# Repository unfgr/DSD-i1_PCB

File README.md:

# DSD-i1_PCB
DSD-i1 DEV/EDU Board Design

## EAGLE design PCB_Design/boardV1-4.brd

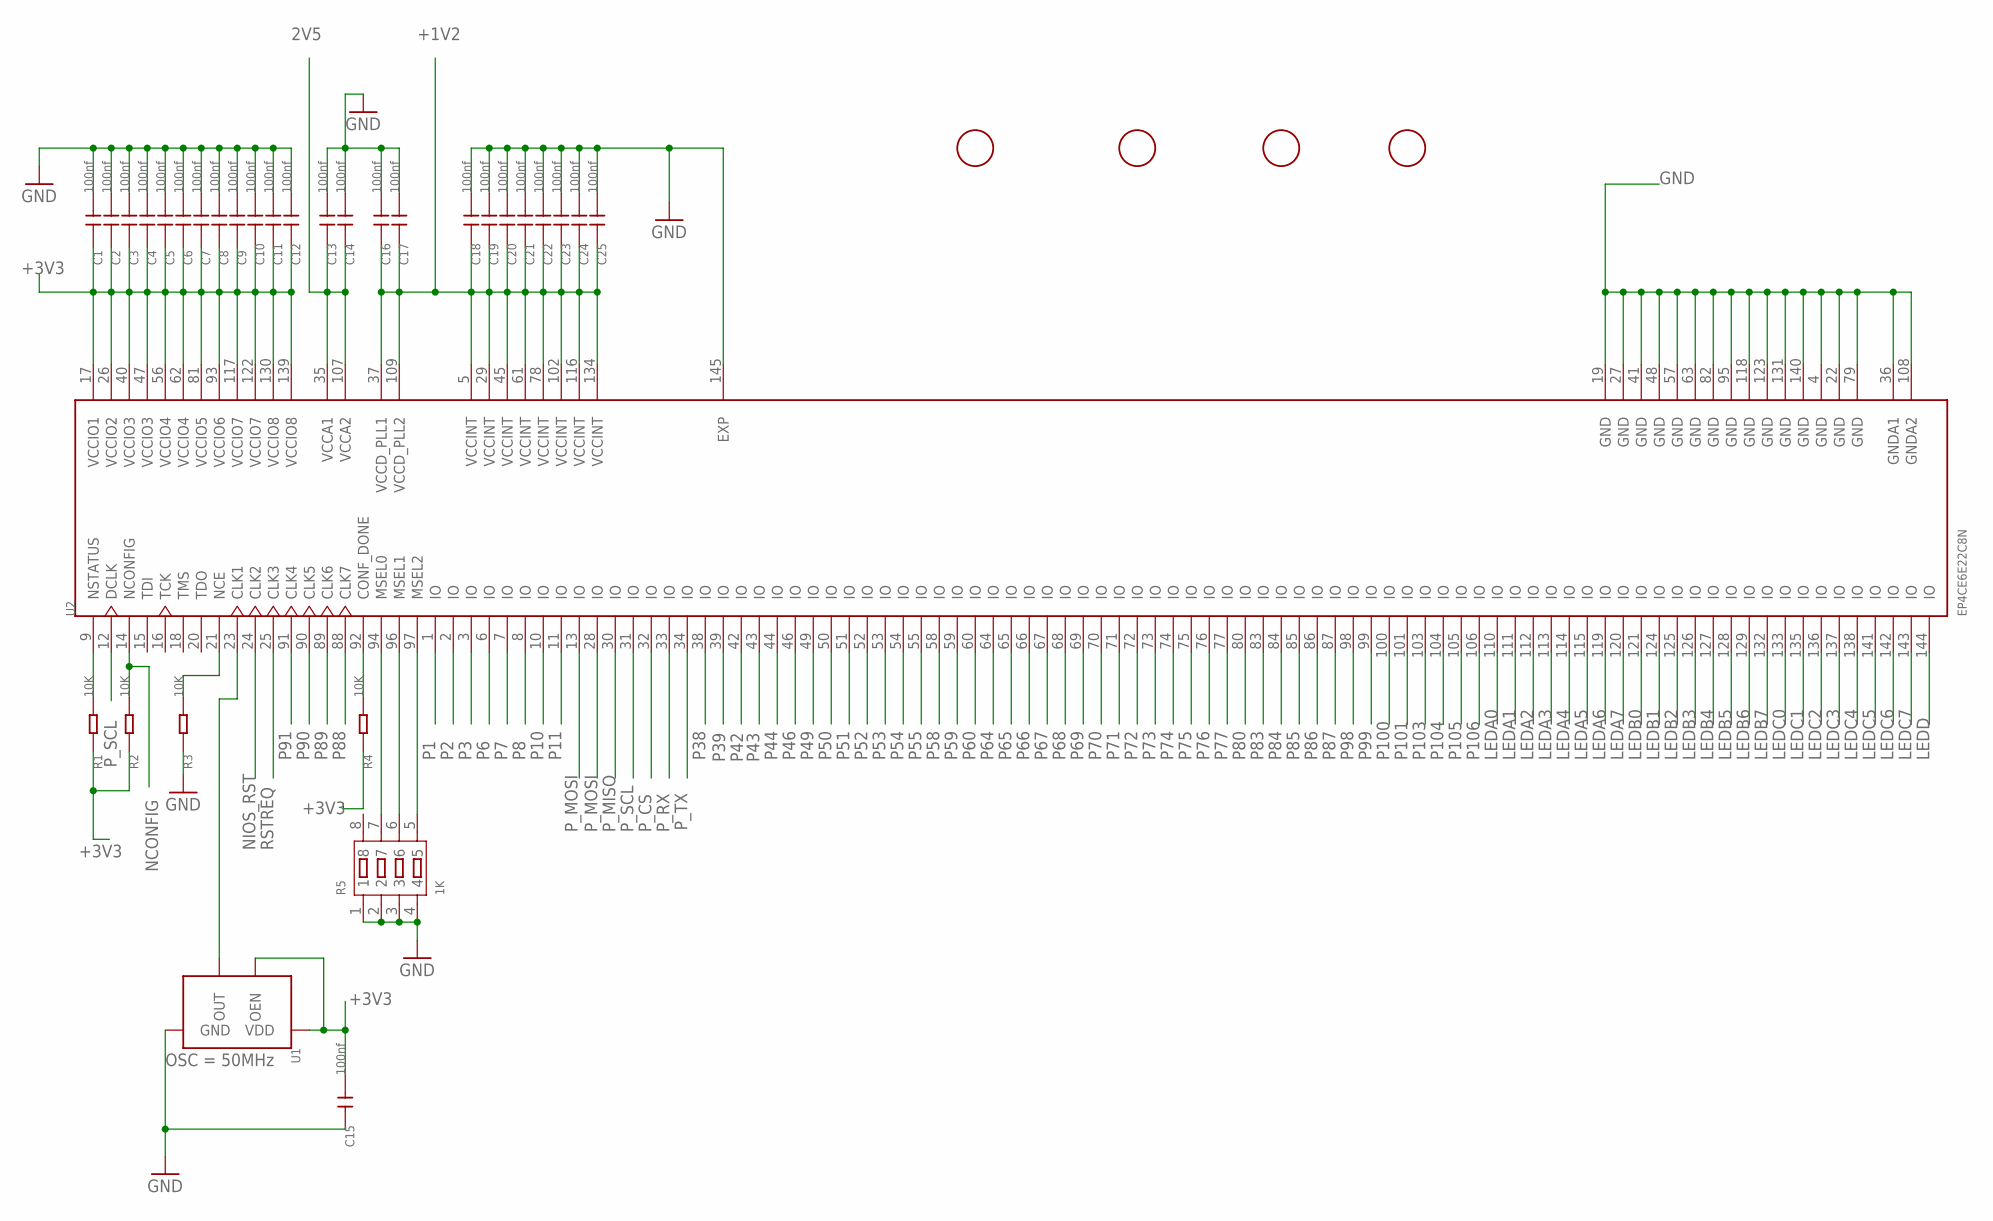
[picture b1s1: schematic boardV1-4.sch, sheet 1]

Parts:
C1, C2, C3, C4, C5, C6, C7, C8, C9, C10, C11, C12, C13, C14, C15, C16, C17, C18, C19, C20, C21, C22, C23, C24, C25: 100nf; C0603
R1, R2, R3, R4: 10K; R0603
R5: 1K; RA1206-8
U1: 306020041_OSC_32.768KHZ-3225_4P; X3225_4P
U2: EP4CE6E22C8N; QFP50P2200X2200X165-145N
U$1, U$2, U$3, U$4: FIDUCIAL; FIDUCIAL_1MM

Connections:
2V5: C13.1, C14.1, U2.35 (VCCA1), U2.107 (VCCA2); also elsewhere on the board
+1V2: C16.1, C17.1, C18.1, C19.1, C20.1, C21.1, C22.1, C23.1, C24.1, C25.1, U2.5 (VCCINT), U2.29 (VCCINT), U2.37 (VCCD_PLL1), U2.45 (VCCINT), U2.61 (VCCINT), U2.78 (VCCINT), U2.102 (VCCINT), U2.109 (VCCD_PLL2), U2.116 (VCCINT), U2.134 (VCCINT); also elsewhere on the board
+3V3: C1.1, C2.1, C3.1, C4.1, C5.1, C6.1, C7.1, C8.1, C9.1, C10.1, C11.1, C12.1, C15.2, R1.1, R2.1, R4.1, U1.P$1 (OEN), U1.P$4 (VDD), U2.17 (VCCIO1), U2.26 (VCCIO2), U2.40 (VCCIO3), U2.47 (VCCIO3), U2.56 (VCCIO4), U2.62 (VCCIO4), U2.81 (VCCIO5), U2.93 (VCCIO6), U2.117 (VCCIO7), U2.122 (VCCIO7), U2.130 (VCCIO8), U2.139 (VCCIO8); also elsewhere on the board
GND: C1.2, C2.2, C3.2, C4.2, C5.2, C6.2, C7.2, C8.2, C9.2, C10.2, C11.2, C12.2, C13.2, C14.2, C15.1, C16.2, C17.2, C18.2, C19.2, C20.2, C21.2, C22.2, C23.2, C24.2, C25.2, R3.1, R5.1, R5.2, R5.3, R5.4, U1.P$2 (GND), U2.4 (GND), U2.19 (GND), U2.22 (GND), U2.27 (GND), U2.36 (GNDA1), U2.41 (GND), U2.48 (GND), U2.57 (GND), U2.63 (GND), U2.79 (GND), U2.82 (GND), U2.95 (GND), U2.108 (GNDA2), U2.118 (GND), U2.123 (GND), U2.131 (GND), U2.140 (GND), U2.145 (EXP); also elsewhere on the board
LEDA0: U2.110 (IO); also elsewhere on the board
LEDA1: U2.111 (IO); also elsewhere on the board
LEDA2: U2.112 (IO); also elsewhere on the board
LEDA3: U2.113 (IO); also elsewhere on the board
LEDA4: U2.114 (IO); also elsewhere on the board
LEDA5: U2.115 (IO); also elsewhere on the board
LEDA6: U2.119 (IO); also elsewhere on the board
LEDA7: U2.120 (IO); also elsewhere on the board
LEDB0: U2.121 (IO); also elsewhere on the board
LEDB1: U2.124 (IO); also elsewhere on the board
LEDB2: U2.125 (IO); also elsewhere on the board
LEDB3: U2.126 (IO); also elsewhere on the board
LEDB4: U2.127 (IO); also elsewhere on the board
LEDB5: U2.128 (IO); also elsewhere on the board
LEDB6: U2.129 (IO); also elsewhere on the board
LEDB7: U2.132 (IO); also elsewhere on the board
LEDC0: U2.133 (IO); also elsewhere on the board
LEDC1: U2.135 (IO); also elsewhere on the board
LEDC2: U2.136 (IO); also elsewhere on the board
LEDC3: U2.137 (IO); also elsewhere on the board
LEDC4: U2.138 (IO); also elsewhere on the board
LEDC5: U2.141 (IO); also elsewhere on the board
LEDC6: U2.142 (IO); also elsewhere on the board
LEDC7: U2.143 (IO); also elsewhere on the board
LEDD: U2.144 (IO); also elsewhere on the board
unnamed: R4.2, U2.92 (CONF_DONE)
unnamed: U1.P$3 (OUT), U2.23 (CLK1)
unnamed: R5.5, U2.97 (MSEL2)
unnamed: R5.6, U2.96 (MSEL1)
unnamed: R5.7, U2.94 (MSEL0)
unnamed: R3.2, U2.21 (NCE)
unnamed: R1.2, U2.9 (NSTATUS)
NCONFIG: R2.2, U2.14 (NCONFIG); also elsewhere on the board
NIOS_RST: U2.24 (CLK2); also elsewhere on the board
P1: U2.1 (IO); also elsewhere on the board
P2: U2.2 (IO); also elsewhere on the board
P3: U2.3 (IO); also elsewhere on the board
P6: U2.6 (IO); also elsewhere on the board
P7: U2.7 (IO); also elsewhere on the board
P8: U2.8 (IO); also elsewhere on the board
P10: U2.10 (IO); also elsewhere on the board
P11: U2.11 (IO); also elsewhere on the board
P38: U2.38 (IO); also elsewhere on the board
P39: U2.39 (IO); also elsewhere on the board
P42: U2.42 (IO); also elsewhere on the board
P43: U2.43 (IO); also elsewhere on the board
P44: U2.44 (IO); also elsewhere on the board
P46: U2.46 (IO); also elsewhere on the board
P49: U2.49 (IO); also elsewhere on the board
P50: U2.50 (IO); also elsewhere on the board
P51: U2.51 (IO); also elsewhere on the board
P52: U2.52 (IO); also elsewhere on the board
P53: U2.53 (IO); also elsewhere on the board
P54: U2.54 (IO); also elsewhere on the board
P55: U2.55 (IO); also elsewhere on the board
P58: U2.58 (IO); also elsewhere on the board
P59: U2.59 (IO); also elsewhere on the board
P60: U2.60 (IO); also elsewhere on the board
P64: U2.64 (IO); also elsewhere on the board
P65: U2.65 (IO); also elsewhere on the board
P66: U2.66 (IO); also elsewhere on the board
P67: U2.67 (IO); also elsewhere on the board
P68: U2.68 (IO); also elsewhere on the board
P69: U2.69 (IO); also elsewhere on the board
P70: U2.70 (IO); also elsewhere on the board
P71: U2.71 (IO); also elsewhere on the board
P72: U2.72 (IO); also elsewhere on the board
P73: U2.73 (IO); also elsewhere on the board
P74: U2.74 (IO); also elsewhere on the board
P75: U2.75 (IO); also elsewhere on the board
P76: U2.76 (IO); also elsewhere on the board
P77: U2.77 (IO); also elsewhere on the board
P80: U2.80 (IO); also elsewhere on the board
P83: U2.83 (IO); also elsewhere on the board
P84: U2.84 (IO); also elsewhere on the board
P85: U2.85 (IO); also elsewhere on the board
P86: U2.86 (IO); also elsewhere on the board
P87: U2.87 (IO); also elsewhere on the board
P88: U2.88 (CLK7); also elsewhere on the board
P89: U2.89 (CLK6); also elsewhere on the board
P90: U2.90 (CLK5); also elsewhere on the board
P91: U2.91 (CLK4); also elsewhere on the board
P98: U2.98 (IO); also elsewhere on the board
P99: U2.99 (IO); also elsewhere on the board
P100: U2.100 (IO); also elsewhere on the board
P101: U2.101 (IO); also elsewhere on the board
P103: U2.103 (IO); also elsewhere on the board
P104: U2.104 (IO); also elsewhere on the board
P105: U2.105 (IO); also elsewhere on the board
P106: U2.106 (IO)
P_CS: U2.32 (IO); also elsewhere on the board
P_MISO: U2.30 (IO); also elsewhere on the board
P_MOSI: U2.13 (IO), U2.28 (IO); also elsewhere on the board
P_RX: U2.33 (IO); also elsewhere on the board
P_SCL: U2.12 (DCLK), U2.31 (IO); also elsewhere on the board
P_TX: U2.34 (IO); also elsewhere on the board
RSTREQ: U2.25 (CLK3); also elsewhere on the board

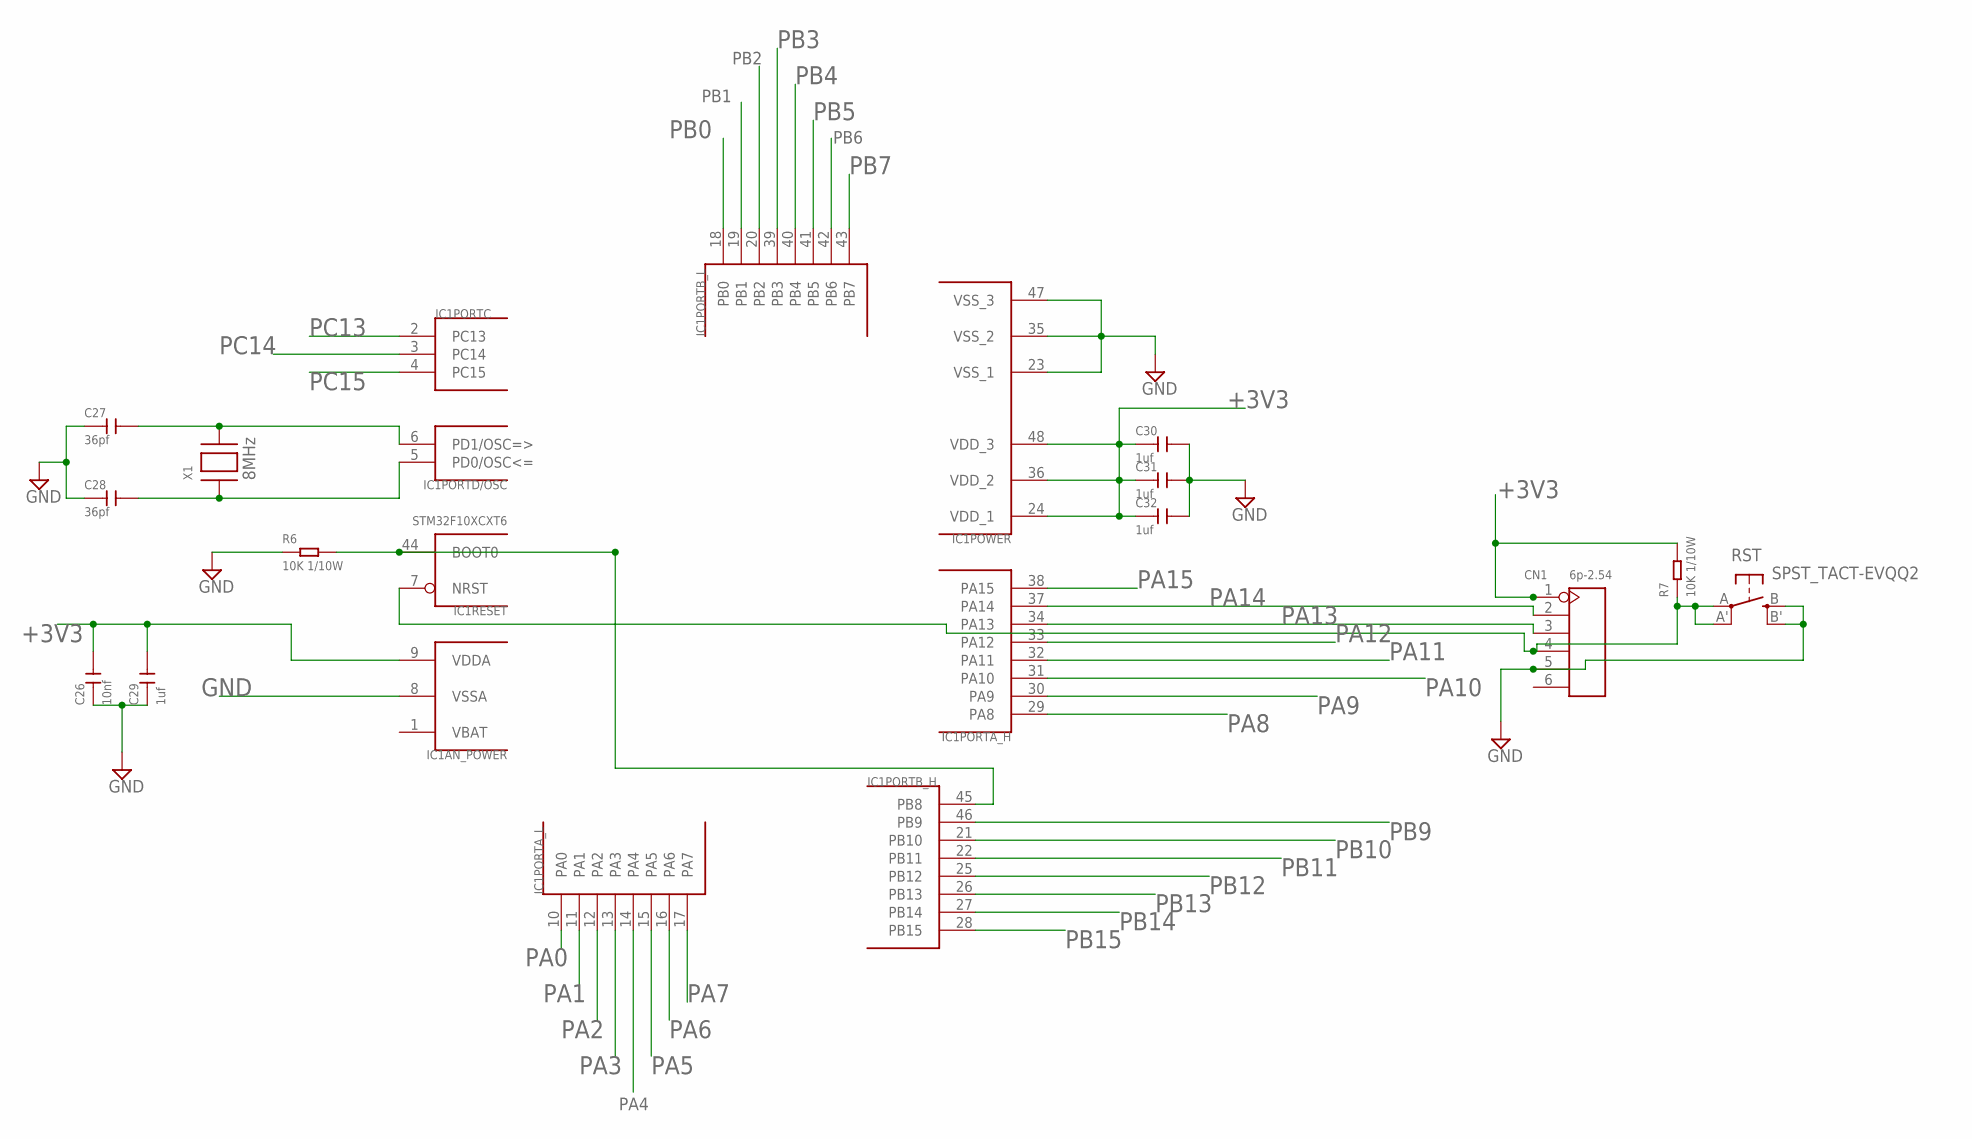
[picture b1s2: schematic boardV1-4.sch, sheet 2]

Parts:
C26: 10nf; C0603
C27, C28: 36pf; C0603
C29, C30, C31, C32: 1uf; C0603
CN1: 6p-2.54; H6-2.54
IC1: STM32F10XCXT6; TQFP48
R6, R7: 10K 1/10W; R0603
RST: SPST_TACT-EVQQ2; EVQ-Q2
X1: 306010047_XTAL_12MHZ-5032_2P; X5032_2P

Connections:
+3V3: C26.2, C29.2, C30.1, C31.1, C32.1, CN1.1, IC1.9 (VDDA), IC1.24 (VDD_1), IC1.36 (VDD_2), IC1.48 (VDD_3), R7.2; also elsewhere on the board
GND: C26.1, C27.1, C28.1, C29.1, C30.2, C31.2, C32.2, CN1.5, IC1.8 (VSSA), IC1.23 (VSS_1), IC1.35 (VSS_2), IC1.47 (VSS_3), R6.1, RST.B (S), RST.B' (S1); also elsewhere on the board
unnamed: IC1.44 (BOOT0), IC1.45 (PB8), R6.2
unnamed: CN1.4, IC1.7 (NRST), R7.1, RST.A, RST.A' (P1)
unnamed: C27.2, IC1.6 (PD1/OSC=>), X1.P$2
unnamed: C28.2, IC1.5 (PD0/OSC<=), X1.P$1
PA0: IC1.10 (PA0); also elsewhere on the board
PA1: IC1.11 (PA1); also elsewhere on the board
PA2: IC1.12 (PA2); also elsewhere on the board
PA3: IC1.13 (PA3); also elsewhere on the board
PA4: IC1.14 (PA4); also elsewhere on the board
PA5: IC1.15 (PA5); also elsewhere on the board
PA6: IC1.16 (PA6); also elsewhere on the board
PA7: IC1.17 (PA7); also elsewhere on the board
PA8: IC1.29 (PA8); also elsewhere on the board
PA9: IC1.30 (PA9); also elsewhere on the board
PA10: IC1.31 (PA10); also elsewhere on the board
PA11: IC1.32 (PA11); also elsewhere on the board
PA12: IC1.33 (PA12); also elsewhere on the board
PA13: CN1.3, IC1.34 (PA13); also elsewhere on the board
PA14: CN1.2, IC1.37 (PA14); also elsewhere on the board
PA15: IC1.38 (PA15); also elsewhere on the board
PB0: IC1.18 (PB0); also elsewhere on the board
PB1: IC1.19 (PB1); also elsewhere on the board
PB2: IC1.20 (PB2); also elsewhere on the board
PB3: IC1.39 (PB3); also elsewhere on the board
PB4: IC1.40 (PB4); also elsewhere on the board
PB5: IC1.41 (PB5); also elsewhere on the board
PB6: IC1.42 (PB6); also elsewhere on the board
PB7: IC1.43 (PB7); also elsewhere on the board
PB9: IC1.46 (PB9); also elsewhere on the board
PB10: IC1.21 (PB10); also elsewhere on the board
PB11: IC1.22 (PB11); also elsewhere on the board
PB12: IC1.25 (PB12); also elsewhere on the board
PB13: IC1.26 (PB13); also elsewhere on the board
PB14: IC1.27 (PB14); also elsewhere on the board
PB15: IC1.28 (PB15); also elsewhere on the board
PC13: IC1.2 (PC13); also elsewhere on the board
PC14: IC1.3 (PC14); also elsewhere on the board
PC15: IC1.4 (PC15); also elsewhere on the board
VBAT: IC1.1 (VBAT)

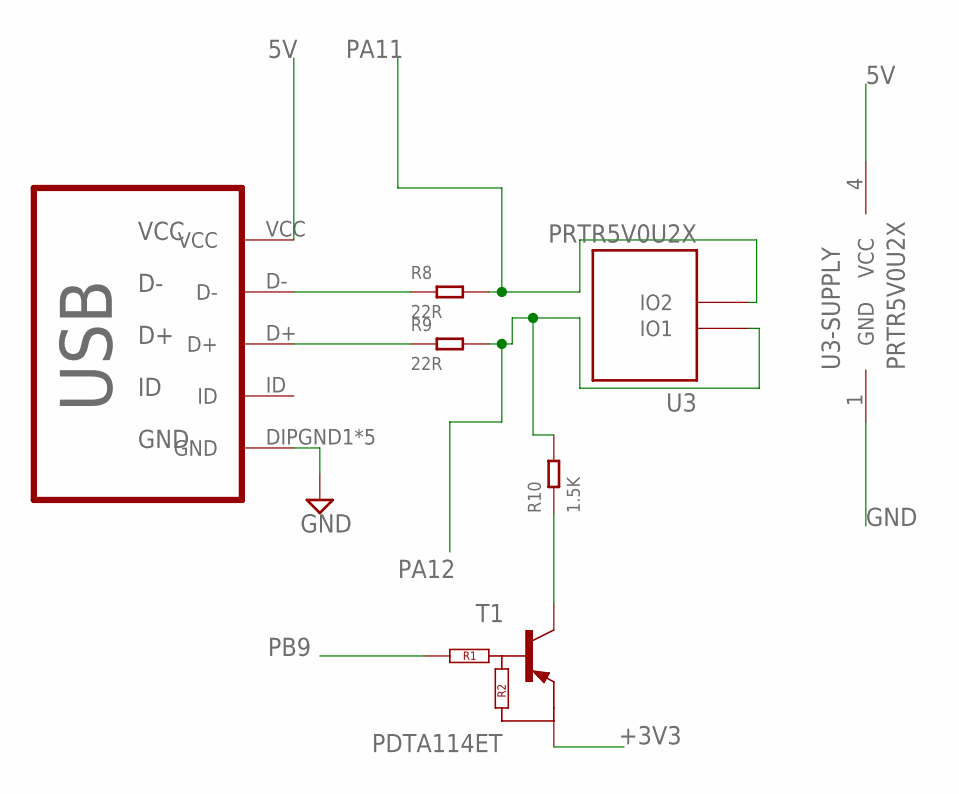
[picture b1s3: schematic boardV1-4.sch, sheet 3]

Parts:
R8, R9: 22R; R0603
R10: 1.5K; R0603
T1: PDTA114ET; SOT23
U3: PRTR5V0U2X; SOT-143B
USB: MICRO-USB-B; MICRO_USB_4_LEGS

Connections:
5V: U3.4 (VCC), USB.VCC; also elsewhere on the board
+3V3: T1.2 (E); also elsewhere on the board
GND: U3.1 (GND), USB.DIPGND1 (GND), USB.DIPGND2 (GND), USB.DIPGND3 (GND), USB.DIPGND4 (GND), USB.GND; also elsewhere on the board
unnamed: R8.1, USB.D-
unnamed: R9.1, USB.D+
unnamed: R10.1, T1.3 (C)
PA11: R8.2, U3.3 (IO2); also elsewhere on the board
PA12: R9.2, R10.2, U3.2 (IO1); also elsewhere on the board
PB9: T1.1 (INPUT); also elsewhere on the board

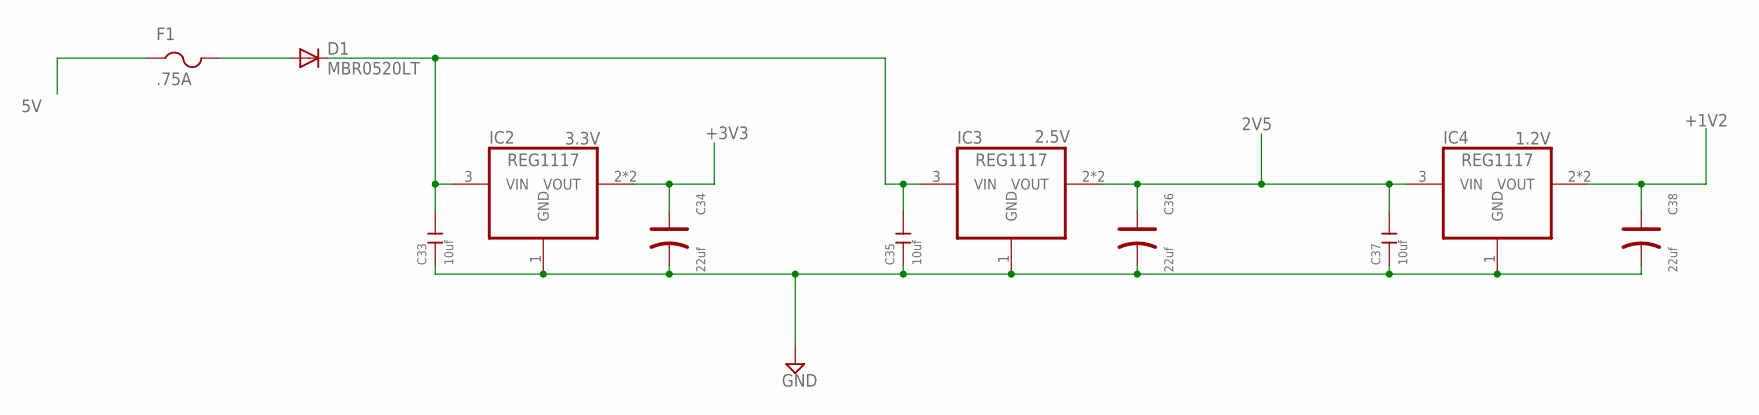
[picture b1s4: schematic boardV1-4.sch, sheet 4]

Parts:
C33, C35, C37: 10uf; C0805
C34, C36, C38: 22uf; AVX-A
D1: MBR0520LT; SOD123
F1: .75A; R1206
IC2, IC3, IC4: REG1117; SOT223

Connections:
2V5: C36.+, C37.2, IC3.2 (VOUT), IC3.4 (VOUT), IC4.3 (VIN); also elsewhere on the board
5V: F1.1; also elsewhere on the board
+1V2: C38.+, IC4.2 (VOUT), IC4.4 (VOUT); also elsewhere on the board
+3V3: C34.+, IC2.2 (VOUT), IC2.4 (VOUT); also elsewhere on the board
GND: C33.1, C34.-, C35.1, C36.-, C37.1, C38.-, IC2.1 (GND), IC3.1 (GND), IC4.1 (GND); also elsewhere on the board
unnamed: C33.2, C35.2, D1.C, IC2.3 (VIN), IC3.3 (VIN)
unnamed: D1.A, F1.2

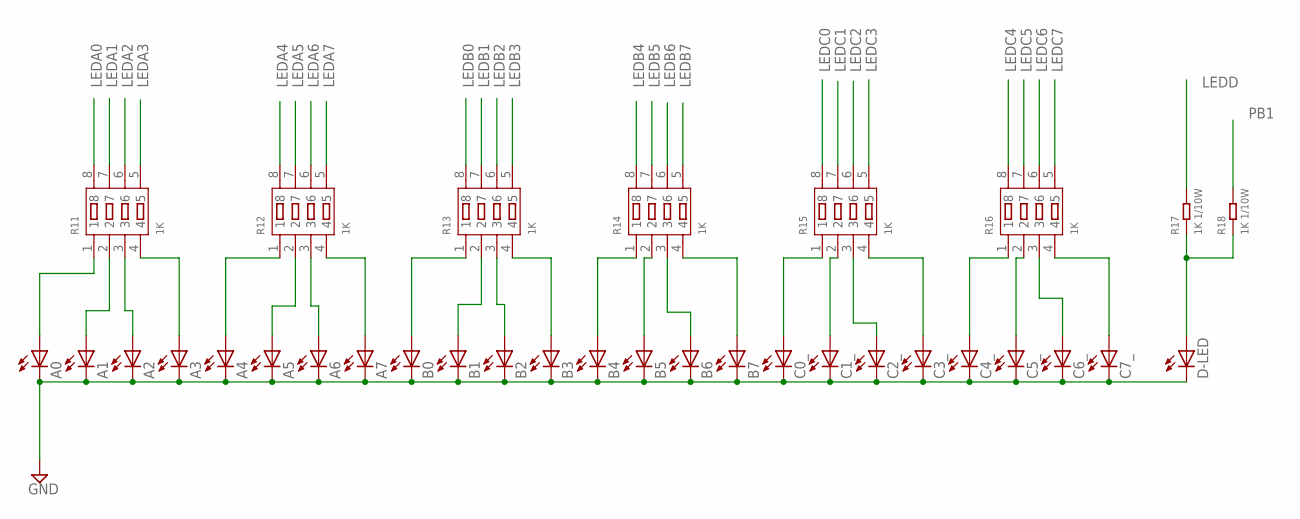
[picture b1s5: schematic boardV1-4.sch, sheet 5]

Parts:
A0, A1, A2, A3, A4, A5, A6, A7: LEDCHIPLED_0603; CHIPLED_0603
B0, B1, B2, B3, B4, B5, B6, B7: LEDCHIPLED_0603; CHIPLED_0603
C0_, C1_, C2_, C3_, C4_, C5_, C6_, C7_: LEDCHIPLED_0603; CHIPLED_0603
D-LED: LEDCHIPLED_0603; CHIPLED_0603
R11, R12, R13, R14, R15, R16: 1K; RA1206-8
R17, R18: 1K 1/10W; R0603

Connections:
GND: A0.C, A1.C, A2.C, A3.C, A4.C, A5.C, A6.C, A7.C, B0.C, B1.C, B2.C, B3.C, B4.C, B5.C, B6.C, B7.C, C0_.C, C1_.C, C2_.C, C3_.C, C4_.C, C5_.C, C6_.C, C7_.C, D-LED.C; also elsewhere on the board
LEDA0: R11.8; also elsewhere on the board
LEDA1: R11.7; also elsewhere on the board
LEDA2: R11.6; also elsewhere on the board
LEDA3: R11.5; also elsewhere on the board
LEDA4: R12.8; also elsewhere on the board
LEDA5: R12.7; also elsewhere on the board
LEDA6: R12.6; also elsewhere on the board
LEDA7: R12.5; also elsewhere on the board
LEDB0: R13.8; also elsewhere on the board
LEDB1: R13.7; also elsewhere on the board
LEDB2: R13.6; also elsewhere on the board
LEDB3: R13.5; also elsewhere on the board
LEDB4: R14.8; also elsewhere on the board
LEDB5: R14.7; also elsewhere on the board
LEDB6: R14.6; also elsewhere on the board
LEDB7: R14.5; also elsewhere on the board
LEDC0: R15.8; also elsewhere on the board
LEDC1: R15.7; also elsewhere on the board
LEDC2: R15.6; also elsewhere on the board
LEDC3: R15.5; also elsewhere on the board
LEDC4: R16.8; also elsewhere on the board
LEDC5: R16.7; also elsewhere on the board
LEDC6: R16.6; also elsewhere on the board
LEDC7: R16.5; also elsewhere on the board
LEDD: R17.2; also elsewhere on the board
unnamed: A7.A, R12.4
unnamed: A0.A, R11.1
unnamed: A1.A, R11.2
unnamed: A2.A, R11.3
unnamed: A3.A, R11.4
unnamed: A4.A, R12.1
unnamed: A5.A, R12.2
unnamed: A6.A, R12.3
unnamed: B0.A, R13.1
unnamed: B1.A, R13.2
unnamed: B2.A, R13.3
unnamed: B3.A, R13.4
unnamed: B4.A, R14.1
unnamed: B5.A, R14.2
unnamed: B6.A, R14.3
unnamed: B7.A, R14.4
unnamed: C0_.A, R15.1
unnamed: C1_.A, R15.2
unnamed: C2_.A, R15.3
unnamed: C3_.A, R15.4
unnamed: C4_.A, R16.1
unnamed: C5_.A, R16.2
unnamed: C6_.A, R16.3
unnamed: C7_.A, R16.4
unnamed: D-LED.A, R17.1, R18.1
PB1: R18.2; also elsewhere on the board

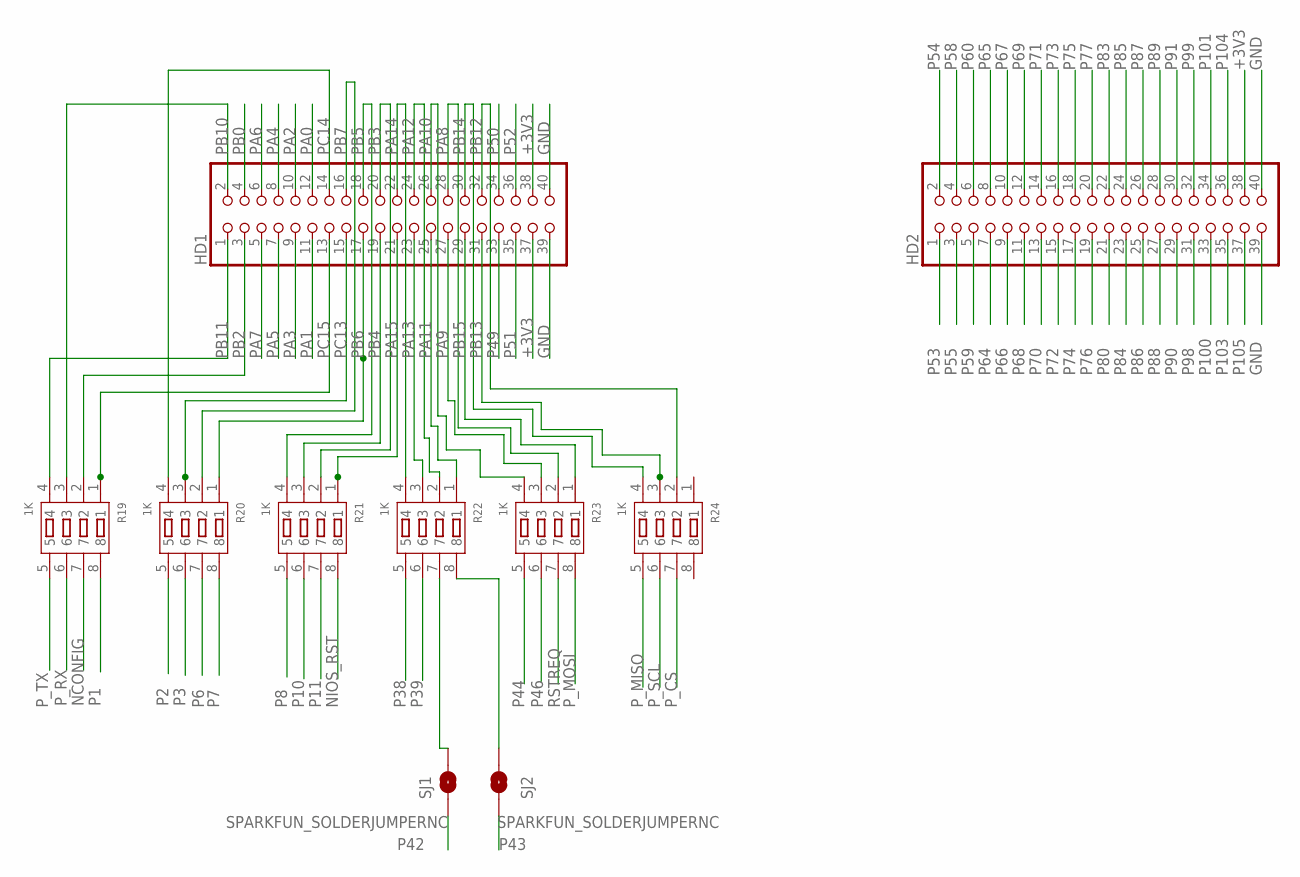
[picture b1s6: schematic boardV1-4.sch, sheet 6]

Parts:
HD1, HD2: PINHD-2X20; 2X20
R19, R20, R21, R22, R23, R24: 1K; RA1206-8
SJ1, SJ2: SPARKFUN_SOLDERJUMPERNC; SPARKFUN_SJ_2S

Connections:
+3V3: HD1.37, HD1.38, HD2.38; also elsewhere on the board
GND: HD1.39, HD1.40, HD2.39, HD2.40; also elsewhere on the board
unnamed: R22.7, SJ1.2
unnamed: R22.8, SJ2.2
NCONFIG: R19.7; also elsewhere on the board
NIOS_RST: R21.8; also elsewhere on the board
P1: R19.8; also elsewhere on the board
P2: R20.5; also elsewhere on the board
P3: R20.6; also elsewhere on the board
P6: R20.7; also elsewhere on the board
P7: R20.8; also elsewhere on the board
P8: R21.5; also elsewhere on the board
P10: R21.6; also elsewhere on the board
P11: R21.7; also elsewhere on the board
P38: R22.5; also elsewhere on the board
P39: R22.6; also elsewhere on the board
P42: SJ1.1; also elsewhere on the board
P43: SJ2.1; also elsewhere on the board
P44: R23.5; also elsewhere on the board
P46: R23.6; also elsewhere on the board
P49: HD1.33; also elsewhere on the board
P50: HD1.34; also elsewhere on the board
P51: HD1.35; also elsewhere on the board
P52: HD1.36; also elsewhere on the board
P53: HD2.1; also elsewhere on the board
P54: HD2.2; also elsewhere on the board
P55: HD2.3; also elsewhere on the board
P58: HD2.4; also elsewhere on the board
P59: HD2.5; also elsewhere on the board
P60: HD2.6; also elsewhere on the board
P64: HD2.7; also elsewhere on the board
P65: HD2.8; also elsewhere on the board
P66: HD2.9; also elsewhere on the board
P67: HD2.10; also elsewhere on the board
P68: HD2.11; also elsewhere on the board
P69: HD2.12; also elsewhere on the board
P70: HD2.13; also elsewhere on the board
P71: HD2.14; also elsewhere on the board
P72: HD2.15; also elsewhere on the board
P73: HD2.16; also elsewhere on the board
P74: HD2.17; also elsewhere on the board
P75: HD2.18; also elsewhere on the board
P76: HD2.19; also elsewhere on the board
P77: HD2.20; also elsewhere on the board
P80: HD2.21; also elsewhere on the board
P83: HD2.22; also elsewhere on the board
P84: HD2.23; also elsewhere on the board
P85: HD2.24; also elsewhere on the board
P86: HD2.25; also elsewhere on the board
P87: HD2.26; also elsewhere on the board
P88: HD2.27; also elsewhere on the board
P89: HD2.28; also elsewhere on the board
P90: HD2.29; also elsewhere on the board
P91: HD2.30; also elsewhere on the board
P98: HD2.31; also elsewhere on the board
P99: HD2.32; also elsewhere on the board
P100: HD2.33; also elsewhere on the board
P101: HD2.34; also elsewhere on the board
P103: HD2.35; also elsewhere on the board
P104: HD2.36; also elsewhere on the board
P105: HD2.37; also elsewhere on the board
PA0: HD1.12; also elsewhere on the board
PA1: HD1.11; also elsewhere on the board
PA2: HD1.10; also elsewhere on the board
PA3: HD1.9; also elsewhere on the board
PA4: HD1.8; also elsewhere on the board
PA5: HD1.7; also elsewhere on the board
PA6: HD1.6; also elsewhere on the board
PA7: HD1.5; also elsewhere on the board
PA8: HD1.28, R23.2; also elsewhere on the board
PA9: HD1.27, R23.3; also elsewhere on the board
PA10: HD1.26, R23.4; also elsewhere on the board
PA11: HD1.25, R22.1; also elsewhere on the board
PA12: HD1.24, R22.2; also elsewhere on the board
PA13: HD1.23, R22.3; also elsewhere on the board
PA14: HD1.22, R22.4; also elsewhere on the board
PA15: HD1.21, R21.1; also elsewhere on the board
PB0: HD1.4; also elsewhere on the board
PB2: HD1.3, R19.2; also elsewhere on the board
PB3: HD1.20, R21.2; also elsewhere on the board
PB4: HD1.19, R21.3; also elsewhere on the board
PB5: HD1.18, R21.4; also elsewhere on the board
PB6: HD1.17, R20.1; also elsewhere on the board
PB7: HD1.16, R20.2; also elsewhere on the board
PB10: HD1.2, R19.3; also elsewhere on the board
PB11: HD1.1, R19.4; also elsewhere on the board
PB12: HD1.32, R24.2; also elsewhere on the board
PB13: HD1.31, R24.3; also elsewhere on the board
PB14: HD1.30, R24.4; also elsewhere on the board
PB15: HD1.29, R23.1; also elsewhere on the board
PC13: HD1.15, R20.3; also elsewhere on the board
PC14: HD1.14, R20.4; also elsewhere on the board
PC15: HD1.13, R19.1; also elsewhere on the board
P_CS: R24.7; also elsewhere on the board
P_MISO: R24.5; also elsewhere on the board
P_MOSI: R23.8; also elsewhere on the board
P_RX: R19.6; also elsewhere on the board
P_SCL: R24.6; also elsewhere on the board
P_TX: R19.5; also elsewhere on the board
RSTREQ: R23.7; also elsewhere on the board

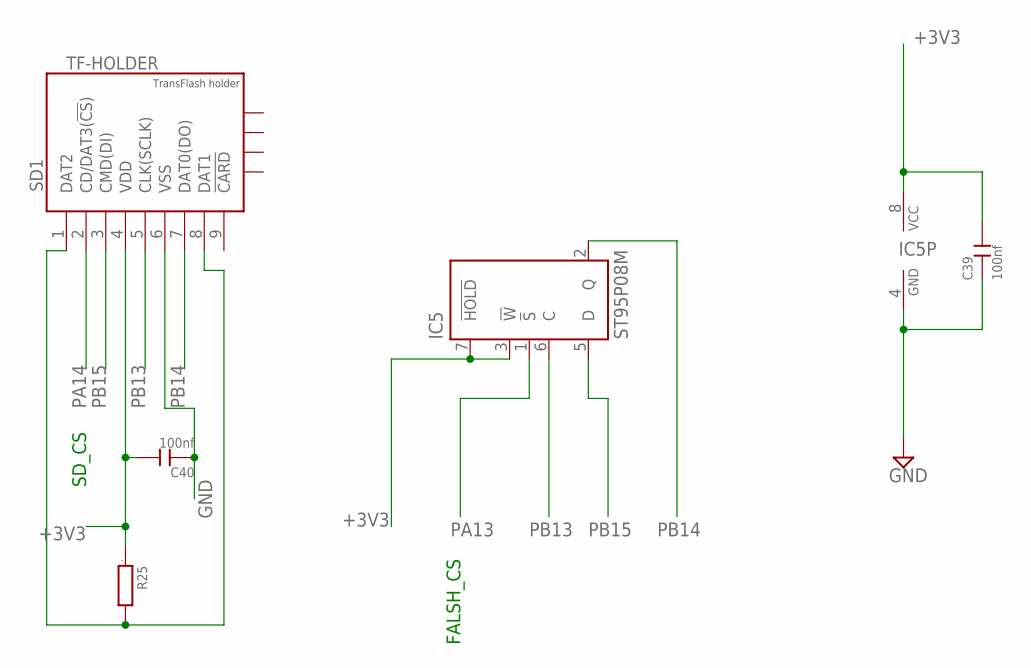
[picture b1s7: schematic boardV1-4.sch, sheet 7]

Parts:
C39, C40: 100nf; C0603
IC5: ST95P08M; SO08
R25: R0603; 0603$1
SD1: TF-HOLDER; TF-PULL

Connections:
+3V3: C39.2, C40.2, IC5.3 (!W), IC5.7 (!HOLD), IC5.8 (VCC), R25.1, SD1.4 (VDD); also elsewhere on the board
GND: C39.1, C40.1, IC5.4 (GND), SD1.6 (VSS); also elsewhere on the board
unnamed: R25.2, SD1.1 (DAT2), SD1.8 (DAT1)
PA13: IC5.1 (!S); also elsewhere on the board
PA14: SD1.2 (CD/DAT3(!CS!)); also elsewhere on the board
PB13: IC5.6 (C), SD1.5 (CLK(SCLK)); also elsewhere on the board
PB14: IC5.2 (Q), SD1.7 (DAT0(DO)); also elsewhere on the board
PB15: IC5.5 (D), SD1.3 (CMD(DI)); also elsewhere on the board

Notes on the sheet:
SD_CS
FALSH_CS

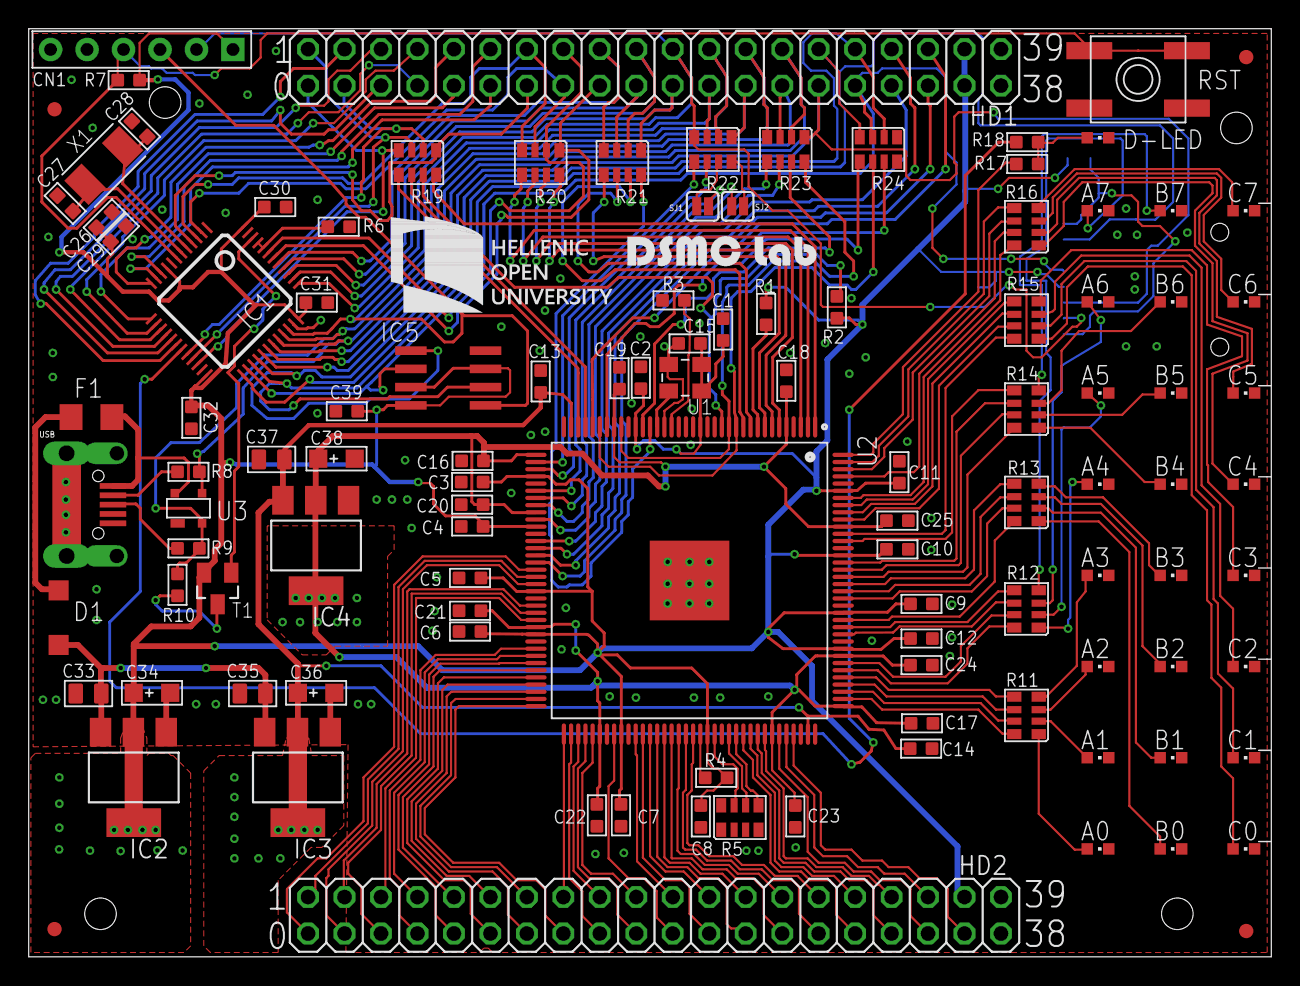
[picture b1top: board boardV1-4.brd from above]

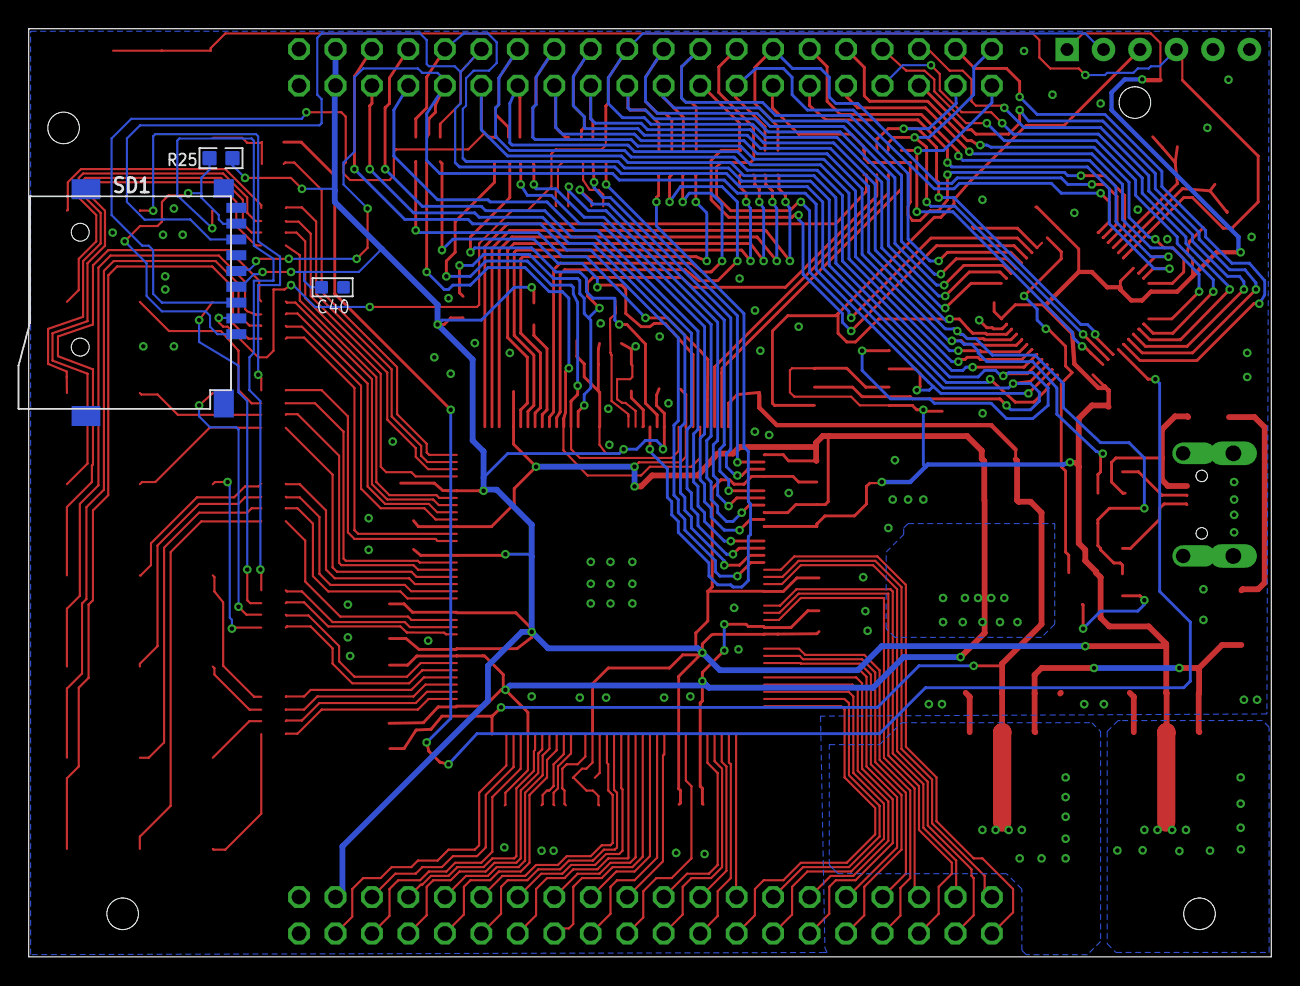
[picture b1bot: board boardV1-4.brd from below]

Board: 2 copper layers, 86.5 x 64.6 mm, 114 parts (3 on the bottom side), 172 nets.

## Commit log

2020-05-22 Minor Corrections

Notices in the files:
parts and their libraries:
Volks73-NXPSemiconductors: Creative Commons Attribution-ShareAlike 3.0 Unported (CC BY-SA 3.0), http://creativecommons.org/licenses/by-sa/3.0/.
